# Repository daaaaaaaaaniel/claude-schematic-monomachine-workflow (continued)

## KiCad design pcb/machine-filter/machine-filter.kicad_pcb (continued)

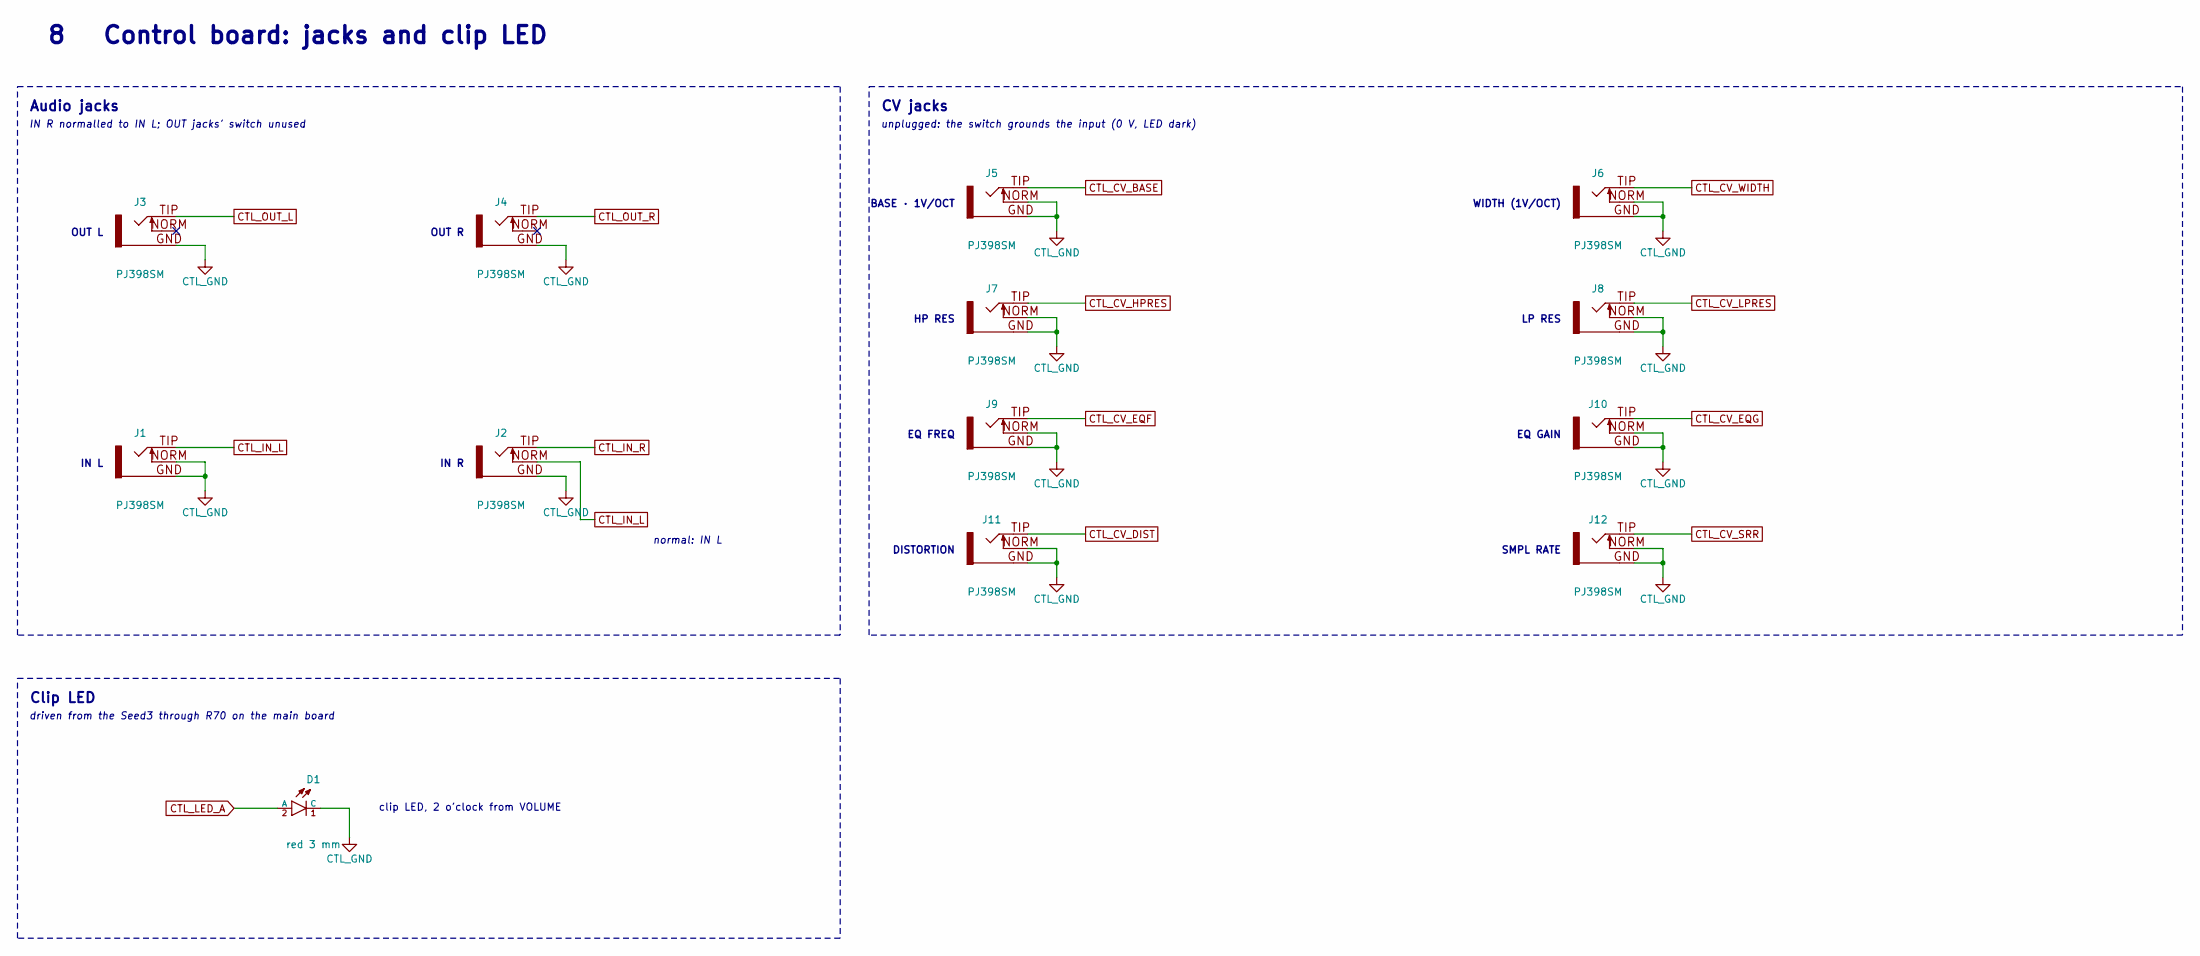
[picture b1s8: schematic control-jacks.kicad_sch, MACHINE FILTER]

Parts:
D1: red 3 mm; LED_3mm_C1A2; MPN 3 mm red LED, diffused
J1, J2, J3, J4: PJ398SM; PJ398SM_Jack_ES; MPN Thonkiconn PJ398SM
J5, J6, J7, J8, J9, J10, J11, J12: PJ398SM; PJ398SM_Jack_4ms_BentGND; MPN Thonkiconn PJ398SM, sleeve leg bent to 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

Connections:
CTL_CV_BASE: J5.TIP; also elsewhere on the board
CTL_CV_DIST: J11.TIP; also elsewhere on the board
CTL_CV_EQF: J9.TIP; also elsewhere on the board
CTL_CV_EQG: J10.TIP; also elsewhere on the board
CTL_CV_HPRES: J7.TIP; also elsewhere on the board
CTL_CV_LPRES: J8.TIP; also elsewhere on the board
CTL_CV_SRR: J12.TIP; also elsewhere on the board
CTL_CV_WIDTH: J6.TIP; also elsewhere on the board
CTL_GND: D1.1 (C), J1.GND, J1.NORM, J2.GND, J3.GND, J4.GND, J5.GND, J5.NORM, J6.GND, J6.NORM, J7.GND, J7.NORM, J8.GND, J8.NORM, J9.GND, J9.NORM, J10.GND, J10.NORM, J11.GND, J11.NORM, J12.GND, J12.NORM; also elsewhere on the board
CTL_IN_L: J1.TIP, J2.NORM; also elsewhere on the board
CTL_IN_R: J2.TIP; also elsewhere on the board
CTL_LED_A: D1.2 (A); also elsewhere on the board
CTL_OUT_L: J3.TIP; also elsewhere on the board
CTL_OUT_R: J4.TIP; also elsewhere on the board

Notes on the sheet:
Audio jacks
IN R normalled to IN L; OUT jacks' switch unused
OUT L
OUT R
IN L
IN R
normal: IN L
CV jacks
unplugged: the switch grounds the input (0 V, LED dark)
BASE · 1V/OCT
WIDTH (1V/OCT)
HP RES
LP RES
EQ FREQ
EQ GAIN
DISTORTION
SMPL RATE
Clip LED
driven from the Seed3 through R70 on the main board
clip LED, 2 o'clock from VOLUME
8 Control board: jacks and clip LED

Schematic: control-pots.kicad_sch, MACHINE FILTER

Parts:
C80: 100n; C_Disc_D3.0mm_W1.6mm_P2.50mm; MPN 100 nF 50 V X7R ceramic, 2.5 mm pitch
RV1, RV2, RV3, RV4, RV5, RV6, RV7, RV8, RV9: B10k; Pot_9mm_SnapIn_ES; MPN Alpha RD901F 9 mm B10k (any shaft)
U6: 74HC4051; SOIC-16_3.9x9.9mm_Pitch1.27mm; MPN 74HC4051D,653; LCSC C9386

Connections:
CTL_+3V3_A: C80.1, RV1.3, RV2.3, RV3.3, RV4.3, RV5.3, RV6.3, RV7.3, RV8.3, RV9.3, U6.16 (VCC); also elsewhere on the board
CTL_GND: C80.2, RV1.1, RV2.1, RV3.1, RV4.1, RV5.1, RV6.1, RV7.1, RV8.1, RV9.1, U6.6 (~E), U6.7 (VEE), U6.8 (GND); also elsewhere on the board
CTL_MUX_A: U6.11 (S0); also elsewhere on the board
CTL_MUX_B: U6.10 (S1); also elsewhere on the board
CTL_MUX_C: U6.9 (S2); also elsewhere on the board
CTL_POT_MUX: U6.3 (A); also elsewhere on the board
CTL_POT_VOL: RV1.2; also elsewhere on the board
unnamed: RV6.2, U6.13 (A0)
unnamed: RV4.2, U6.14 (A1)
unnamed: RV2.2, U6.15 (A2)
unnamed: RV8.2, U6.12 (A3)
unnamed: RV3.2, U6.1 (A4)
unnamed: RV9.2, U6.5 (A5)
unnamed: RV5.2, U6.2 (A6)
unnamed: RV7.2, U6.4 (A7)

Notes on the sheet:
Pots and pot multiplexer
pots: CCW end to GND, CW end to +3V3_A (from the main board); VOLUME has its own ADC pin, the other eight share one
EQ FREQ
HP RES
BASE · 1V/OCT
DISTORTION
WIDTH (1V/OCT)
SMPL RATE
LP RES
EQ GAIN
VOLUME
U6 passes one of the 8 pot wipers to POT_MUX; the Seed selects it with MUX_A/B/C (S0/S1/S2).
CTL_POT_MUX, CTL_POT_VOL, CTL_MUX_A/B/C go to the Seed3 on the main board, through the board connector (page 12).
Channel order follows the floorplan (design/pinmap.py); the firmware maps it.
9 Control board: pots and pot multiplexer

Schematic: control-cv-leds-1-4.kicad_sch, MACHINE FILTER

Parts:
C81, C82: 100n; C_Disc_D3.0mm_W1.6mm_P2.50mm; MPN 100 nF 50 V X7R ceramic, 2.5 mm pitch
D2, D3, D4, D5: red/green 3 mm; LED_3mm_Raised; MPN 3 mm red/green bicolour LED, 2 leads (a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
R71, R72, R73, R74: 1.5k; R_Axial_DIN0204_L3.6mm_D1.6mm_P5.08mm_Horizontal; MPN 1.5k 1/8 W 1% metal film, axial DIN0204
R80, R81, R82, R83: 10k; R_Axial_DIN0204_L3.6mm_D1.6mm_P5.08mm_Horizontal; MPN 10k 1/8 W 1% metal film, axial DIN0204
R90, R91, R92, R93: 1M; R_Axial_DIN0204_L3.6mm_D1.6mm_P5.08mm_Horizontal; MPN 1M 1/8 W 1% metal film, axial DIN0204
U7: LM324; SOIC-14_3.9x8.65mm_Pitch1.27mm; MPN LM324DT; LCSC C71035

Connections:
CTL_+12V: C81.1, U7.4 (V+); also elsewhere on the board
CTL_-12V: C82.2, U7.11 (V-); also elsewhere on the board
CTL_CV_BASE: R80.1; also elsewhere on the board
CTL_CV_HPRES: R82.1; also elsewhere on the board
CTL_CV_LPRES: R83.1; also elsewhere on the board
CTL_CV_WIDTH: R81.1; also elsewhere on the board
CTL_GND: C81.2, C82.1, R71.2, R72.2, R73.2, R74.2, R90.2, R91.2, R92.2, R93.2; also elsewhere on the board
unnamed: D2.2 (AK), R71.1, U7.13 (-)
unnamed: D2.1 (KA), U7.14
unnamed: D3.2 (AK), R72.1, U7.2 (-)
unnamed: D3.1 (KA), U7.1
unnamed: D4.2 (AK), R73.1, U7.9 (-)
unnamed: D4.1 (KA), U7.8
unnamed: D5.2 (AK), R74.1, U7.6 (-)
unnamed: D5.1 (KA), U7.7
unnamed: R81.2, R91.1, U7.3 (+)
unnamed: R83.2, R93.1, U7.5 (+)
unnamed: R82.2, R92.1, U7.10 (+)
unnamed: R80.2, R90.1, U7.12 (+)

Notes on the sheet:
CV 1: BASE · 1V/OCT LED
LED current = CV / 1.5k
green +, red -
CV 2: WIDTH (1V/OCT) LED
CV 3: HP RES LED
CV 4: LP RES LED
Op-amp supplies
U7: LM324, LED drivers
Each CV jack also lights a 2-lead red/green LED by it:
an LM324 with the LED in its feedback loop (after Mutable Instruments' Shades):
LED current = CV / 1.5k, no dead zone, levelling off near 5.5-6 mA from about ±8.5 V.
10k: input protection; 1M: an undriven cable reads 0 V, LED dark.
Through-hole resistors and capacitors (hand-soldered); U7, U8 SOIC (hand-soldered).
10 Control board: CV LEDs 1-4, LED drivers

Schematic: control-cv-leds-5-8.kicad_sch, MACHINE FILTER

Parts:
C83, C84: 100n; C_Disc_D3.0mm_W1.6mm_P2.50mm; MPN 100 nF 50 V X7R ceramic, 2.5 mm pitch
D6, D7, D8, D9: red/green 3 mm; LED_3mm_Raised; MPN 3 mm red/green bicolour LED, 2 leads (a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
R75, R76, R77, R78: 1.5k; R_Axial_DIN0204_L3.6mm_D1.6mm_P5.08mm_Horizontal; MPN 1.5k 1/8 W 1% metal film, axial DIN0204
R84, R85, R86, R87: 10k; R_Axial_DIN0204_L3.6mm_D1.6mm_P5.08mm_Horizontal; MPN 10k 1/8 W 1% metal film, axial DIN0204
R94, R95, R96, R97: 1M; R_Axial_DIN0204_L3.6mm_D1.6mm_P5.08mm_Horizontal; MPN 1M 1/8 W 1% metal film, axial DIN0204
U8: LM324; SOIC-14_3.9x8.65mm_Pitch1.27mm; MPN LM324DT; LCSC C71035

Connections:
CTL_+12V: C83.1, U8.4 (V+); also elsewhere on the board
CTL_-12V: C84.2, U8.11 (V-); also elsewhere on the board
CTL_CV_DIST: R86.1; also elsewhere on the board
CTL_CV_EQF: R84.1; also elsewhere on the board
CTL_CV_EQG: R85.1; also elsewhere on the board
CTL_CV_SRR: R87.1; also elsewhere on the board
CTL_GND: C83.2, C84.1, R75.2, R76.2, R77.2, R78.2, R94.2, R95.2, R96.2, R97.2; also elsewhere on the board
unnamed: D6.2 (AK), R75.1, U8.13 (-)
unnamed: D6.1 (KA), U8.14
unnamed: D7.2 (AK), R76.1, U8.2 (-)
unnamed: D7.1 (KA), U8.1
unnamed: D8.2 (AK), R77.1, U8.9 (-)
unnamed: D8.1 (KA), U8.8
unnamed: D9.2 (AK), R78.1, U8.6 (-)
unnamed: D9.1 (KA), U8.7
unnamed: R85.2, R95.1, U8.3 (+)
unnamed: R87.2, R97.1, U8.5 (+)
unnamed: R86.2, R96.1, U8.10 (+)
unnamed: R84.2, R94.1, U8.12 (+)

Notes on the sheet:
CV 5: EQ FREQ LED
LED current = CV / 1.5k
green +, red -
CV 6: EQ GAIN LED
CV 7: DISTORTION LED
CV 8: SMPL RATE LED
Op-amp supplies
U8: LM324, LED drivers
Each CV jack also lights a 2-lead red/green LED by it:
an LM324 with the LED in its feedback loop (after Mutable Instruments' Shades):
LED current = CV / 1.5k, no dead zone, levelling off near 5.5-6 mA from about ±8.5 V.
10k: input protection; 1M: an undriven cable reads 0 V, LED dark.
Through-hole resistors and capacitors (hand-soldered); U7, U8 SOIC (hand-soldered).
11 Control board: CV LEDs 5-8, LED drivers

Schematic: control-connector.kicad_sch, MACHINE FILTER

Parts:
JA1, JA3: 1x7 socket; PinSocket_1x07_P2.54mm_Vertical; MPN 2.54 mm female header 1x7, 8.5 mm (as t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
JA2: 1x11 socket; PinSocket_1x11_P2.54mm_Vertical; MPN 2.54 mm female header 1x11, 8.5 mm (as 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
JA4: 1x9 socket; PinSocket_1x09_P2.54mm_Vertical; MPN 2.54 mm female header 1x9, 8.5 mm (as t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

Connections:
CTL_+3V3_A: JA2.4; also elsewhere on the board
CTL_+12V: JA3.2; also elsewhere on the board
CTL_-12V: JA4.2; also elsewhere on the board
CTL_CV_BASE: JA2.9; also elsewhere on the board
CTL_CV_DIST: JA4.7; also elsewhere on the board
CTL_CV_EQF: JA4.8; also elsewhere on the board
CTL_CV_EQG: JA4.5; also elsewhere on the board
CTL_CV_HPRES: JA2.6; also elsewhere on the board
CTL_CV_LPRES: JA2.7; also elsewhere on the board
CTL_CV_SRR: JA4.4; also elsewhere on the board
CTL_CV_WIDTH: JA2.10; also elsewhere on the board
CTL_GND: JA1.1, JA1.4, JA1.6, JA2.3, JA2.5, JA2.8, JA2.11, JA3.1, JA3.3, JA4.1, JA4.3, JA4.6, JA4.9; also elsewhere on the board
CTL_IN_L: JA1.5; also elsewhere on the board
CTL_IN_R: JA1.7; also elsewhere on the board
CTL_LED_A: JA3.4; also elsewhere on the board
CTL_MUX_A: JA3.5; also elsewhere on the board
CTL_MUX_B: JA3.7; also elsewhere on the board
CTL_MUX_C: JA3.6; also elsewhere on the board
CTL_OUT_L: JA1.3; also elsewhere on the board
CTL_OUT_R: JA1.2; also elsewhere on the board
CTL_POT_MUX: JA2.1; also elsewhere on the board
CTL_POT_VOL: JA2.2; also elsewhere on the board

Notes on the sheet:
Board-to-board connector
4 single-row 2.54 mm headers: JA* female on the control board's back, JB* male on the main board's front
JA1: pin 1 at (36.83, 16.51) mm,
panel frame; pins run down (main side)
JA2: pin 1 at (43.18, 52.07) mm,
panel frame; pins run up (main side)
JA3: pin 1 at (5.08, 55.88) mm,
panel frame; pins run right (main side)
JA4: pin 1 at (43.18, 110.49) mm,
Supplies from the main board (PWR_FLAG: driven through the connector)
Header groups, positions and pin order come from the floorplan (design/headers.py): analog pairs, then digital pairs, a GND after each pair; supplies between GNDs.
12 Control board: board-to-board connector

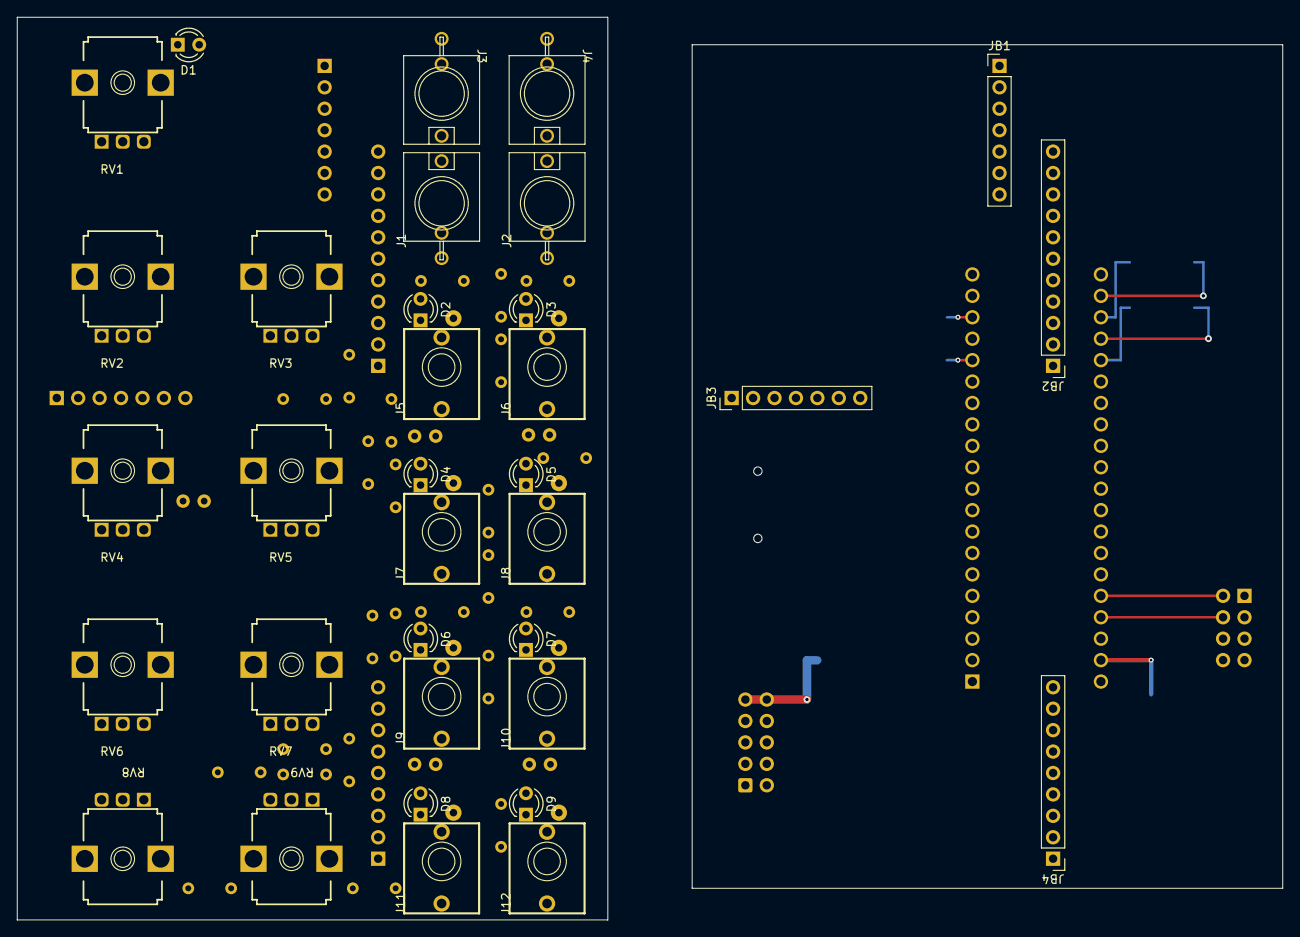
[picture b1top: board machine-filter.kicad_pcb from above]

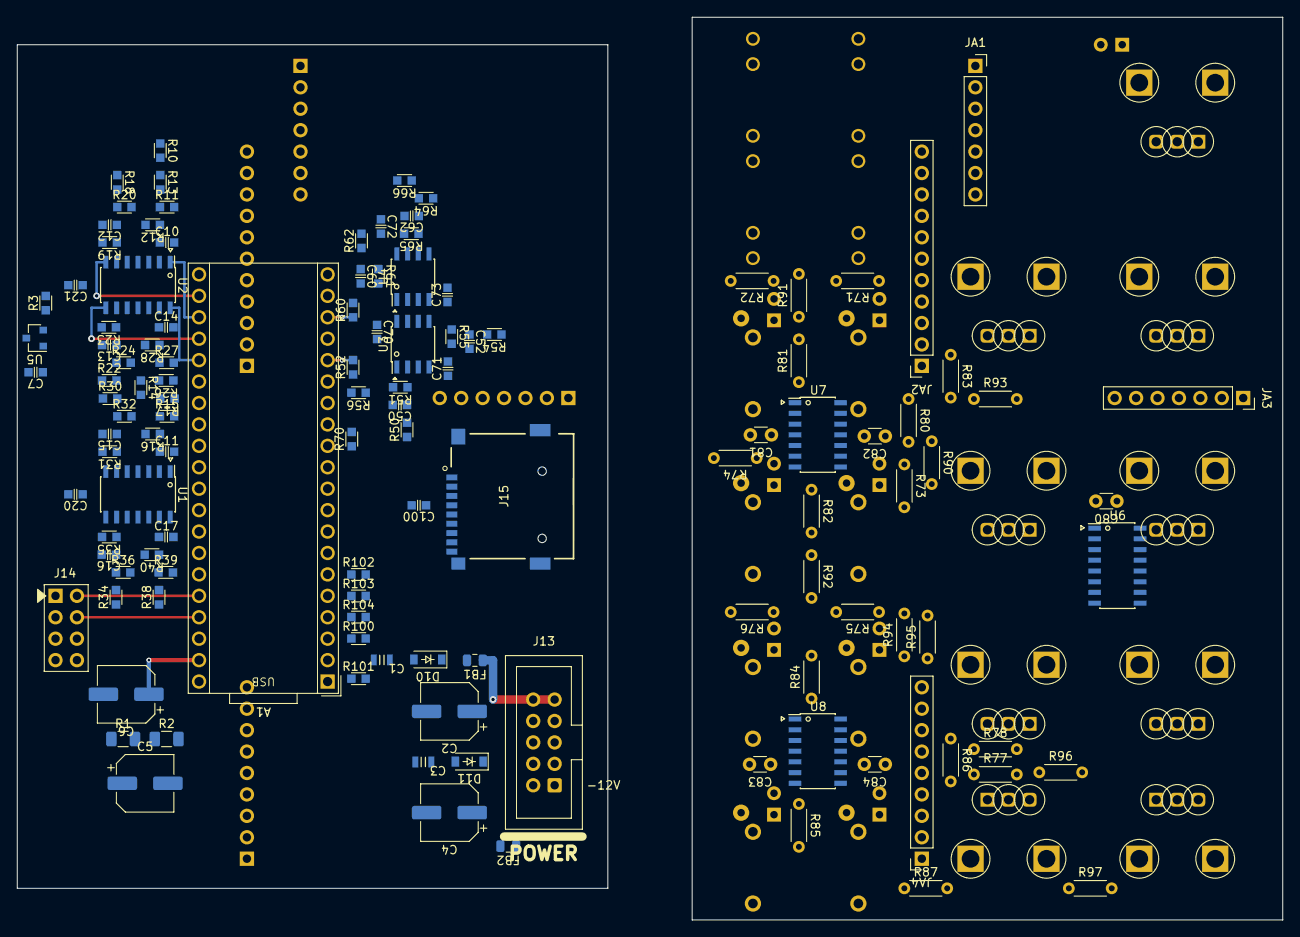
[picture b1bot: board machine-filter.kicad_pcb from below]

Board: 2 copper layers, 150.0 x 107.0 mm, 156 parts (122 on the bottom side), 125 nets.

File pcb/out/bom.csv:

"Reference","Value","Footprint","LCSC","MPN","Board","Assembly","DNP","QUANTITY"
"A1","Daisy Seed3","filter-module:Daisy_Seed_ES_Sockets","","Electrosmith Daisy Seed3 on 2x 1x20 2.54 mm sockets","main","hand","","1"
"C1,C3","10u 25V","filter-module:C_0805","C15850","CL21A106KAYNNNE","main","JLC (SMD)","","2"
"C2,C4-C6","100u 35V","Capacitor_SMD:CP_Elec_6.3x7.7","C72478","RVT1V101M0607","main","JLC (SMD)","","4"
"C7,C20,C21,C70-C73,C100","100n","filter-module:C_0603","C14663","CC0603KRX7R9BB104","main","JLC (SMD)","","8"
"C10-C17","1n","filter-module:C_0603","C1588","CL10B102KB8NNNC","main","JLC (SMD)","","8"
"C50,C52","330p","filter-module:C_0603","C1664","CL10C331JB8NNNC","main","JLC (SMD)","","2"
"C60,C62","47p","filter-module:C_0603","C1671","CL10C470JB8NNNC","main","JLC (SMD)","","2"
"C80-C84","100n","Capacitor_THT:C_Disc_D3.0mm_W1.6mm_P2.50mm","","100 nF 50 V X7R ceramic, 2.5 mm pitch","control","hand","","5"
"D1","red 3 mm","filter-module:LED_3mm_C1A2","","3 mm red LED, diffused","control","hand","","1"
"D2-D9","red/green 3 mm","filter-module:LED_3mm_Raised","","3 mm red/green bicolour LED, 2 leads (anti-parallel), diffused","control","hand","","8"
"D10,D11","B5819W","filter-module:D_SOD-123","C8598","B5819W SL","main","JLC (SMD)","","2"
"FB1,FB2","600R@100MHz 0.5A","filter-module:R_0805_2012Metric","C1017","GZ2012D601TF","main","JLC (SMD)","","2"
"J1-J4","PJ398SM","filter-module:PJ398SM_Jack_ES","","Thonkiconn PJ398SM","control","hand","","4"
"J5-J12","PJ398SM","filter-module:PJ398SM_Jack_4ms_BentGND","","Thonkiconn PJ398SM, sleeve leg bent to the footprint","control","hand","","8"
"J13","EURO PWR 2x5","filter-module:Pins_2x05_2.54mm_TH_EurorackPower_Shrouded","","2x5 2.54 mm shrouded box header","main","hand","","1"
"J14","EXPANSION 2x4","filter-module:Pins_2x04_2.54mm_TH","","2x4 2.54 mm pin header, unshrouded (d)","main","hand","","1"
"J15","TF-01A","filter-module:TF-01A","C91145","HRO TF-01A microSD socket, push-push (optional, DNP)","main","JLC (SMD)","DNP","1"
"JA1,JA3","1x7 socket","Connector_PinSocket_2.54mm:PinSocket_1x07_P2.54mm_Vertical","","2.54 mm female header 1x7, 8.5 mm (as the Seed3 sockets)","control","hand","","2"
"JA2","1x11 socket","Connector_PinSocket_2.54mm:PinSocket_1x11_P2.54mm_Vertical","","2.54 mm female header 1x11, 8.5 mm (as the Seed3 sockets)","control","hand","","1"
"JA4","1x9 socket","Connector_PinSocket_2.54mm:PinSocket_1x09_P2.54mm_Vertical","","2.54 mm female header 1x9, 8.5 mm (as the Seed3 sockets)","control","hand","","1"
"JB1,JB3","1x7 header","Connector_PinHeader_2.54mm:PinHeader_1x07_P2.54mm_Vertical","","2.54 mm male pin header 1x7","main","hand","","2"
"JB2","1x11 header","Connector_PinHeader_2.54mm:PinHeader_1x11_P2.54mm_Vertical","","2.54 mm male pin header 1x11","main","hand","","1"
"JB4","1x9 header","Connector_PinHeader_2.54mm:PinHeader_1x09_P2.54mm_Vertical","","2.54 mm male pin header 1x9","main","hand","","1"
"R1,R2","3.3 0.75W","filter-module:R_1206_3216Metric","C2577888","SG73P2BTTD3R30F","main","JLC (SMD)","","2"
"R3,R70","1k","filter-module:R_0603","C21190","0603WAF1001T5E","main","JLC (SMD)","","2"
"R10,R14","100k 0.1%","filter-module:R_0603","C122538","RT0603BRD07100KL","main","JLC (SMD)","","2"
"R11,R13,R15,R17","20k 0.1%","filter-module:R_0603","C723637","RT0603BRD0720KL","main","JLC (SMD)","","4"
"R12,R16","120k 25ppm","filter-module:R_0603","C862537","RT0603DRD07120KL","main","JLC (SMD)","","2"
"R18,R20,R22,R24,R26,R28,R30,R32,R34,R36,R38,R40","120k","filter-module:R_0603","C25808","0603WAF1203T5E","main","JLC (SMD)","","12"
"R19,R23,R27,R31,R35,R39","20k","filter-module:R_0603","C4184","0603WAF2002T5E","main","JLC (SMD)","","6"
"R50,R54","100k","filter-module:R_0603","C25803","0603WAF1003T5E","main","JLC (SMD)","","2"
"R51,R55,R60,R64","10k","filter-module:R_0603","C25804","0603WAF1002T5E","main","JLC (SMD)","","4"
"R52,R56,R62,R66","100","filter-module:R_0603","C22775","0603WAF1000T5E","main","JLC (SMD)","","4"
"R61,R65","51k","filter-module:R_0603","C23196","0603WAF5102T5E","main","JLC (SMD)","","2"
"R71-R78","1.5k","Resistor_THT:R_Axial_DIN0204_L3.6mm_D1.6mm_P5.08mm_Horizontal","","1.5k 1/8 W 1% metal film, axial DIN0204","control","hand","","8"
"R80-R87","10k","Resistor_THT:R_Axial_DIN0204_L3.6mm_D1.6mm_P5.08mm_Horizontal","","10k 1/8 W 1% metal film, axial DIN0204","control","hand","","8"
"R90-R97","1M","Resistor_THT:R_Axial_DIN0204_L3.6mm_D1.6mm_P5.08mm_Horizontal","","1M 1/8 W 1% metal film, axial DIN0204","control","hand","","8"
"R100-R104","47k","filter-module:R_0603","C25819","0603WAF4702T5E","main","JLC (SMD)","","5"
"RV1-RV9","B10k","filter-module:Pot_9mm_SnapIn_ES","","Alpha RD901F 9 mm B10k (any shaft)","control","hand","","9"
"U1,U2","LMV324","filter-module:SOIC-14_3.9x8.65mm_Pitch1.27mm","C7974","LMV324IDR","main","JLC (SMD)","","2"
"U3,U4","TL072","filter-module:SOIC-8_3.9x4.9mm_Pitch1.27mm","C6961","TL072CDT","main","JLC (SMD)","","2"
"U5","LM4040-10","filter-module:SOT-23","C201738","LM4040C10IDBZR","main","JLC (SMD)","","1"
"U6","74HC4051","filter-module:SOIC-16_3.9x9.9mm_Pitch1.27mm","C9386","74HC4051D,653","control","hand","","1"
"U7,U8","LM324","filter-module:SOIC-14_3.9x8.65mm_Pitch1.27mm","C71035","LM324DT","control","hand","","2"

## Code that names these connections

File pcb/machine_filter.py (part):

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
# Seed3 pins (Electrosmith Seed3_pinout.csv). ADC pins from design/pinmap.py; MIDI on pins 14/15 (D13/D14, USART1).
# Which pins may trade places: design/swap_groups.py.
SEED_PINS = {"2": "SD_D3", "3": "SD_D2", "4": "SD_D1", "5": "SD_D0", "6": "SD_CMD", "7": "SD_CK", "8": "MUX_A", "9": "MUX_B", "10": "MUX_C", "12": "LED_CLIP",
             "16": "CODEC_IN_L", "17": "CODEC_IN_R", "18": "CODEC_OUT_L", "19": "CODEC_OUT_R",
             "36": "USB_DM", "37": "USB_DP"}
SEED_PINS.update({pin: sig for sig, pin in PM.SEED_ADC.items()})
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    j14 = stock("Connector_Generic", "Conn_02x04_Odd_Even", "J14", "EXPANSION 2x4", f"{FM}:Pins_2x04_2.54mm_TH",
                mpn="2x4 2.54 mm pin header, unshrouded")
    # D+ on pin 4, ground on pin 3 (d, 2026-10-07): both USB lines reach the near pin column in a straight line
    for pin, net in {"2": "USB_DM", "4": "USB_DP", "5": "MIDI_TX", "6": "MIDI_RX"}.items():
        j14[pin] += N(net)
    j14[1, 3, 8] += GND
    j14[7] += D33
    # optional microSD socket (as the Dev Kit): SDMMC1 on pins 2-7, 47k pull-ups on CMD and D0-D3; the socket is DNP
    j15 = stock(FM, "MicroSD_TF-01A", "J15", "TF-01A", f"{FM}:TF-01A", "C91145",
                "HRO TF-01A microSD socket, push-push (optional, DNP)")
    for pin, net in {"1": "SD_D2", "2": "SD_D3", "3": "SD_CMD", "5": "SD_CK", "7": "SD_D0", "8": "SD_D1"}.items():
        j15[pin] += N(net)
    j15["4"] += D33
    j15["6", "MP1", "MP2", "MP3", "MP4"] += GND
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
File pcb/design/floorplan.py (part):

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    adc_unit, _ = match(CV, slots, lambda n, qs: dist(hpin[f"CV_{n}"], P(quads[qs[0]], SECTION[qs[1]][1])))
    # signals -> ADC pins (weighted: the scaled side is sensitive; the 1V/OCT inputs most of all)
    src = {f"ADC_{n}": P(quads[adc_unit[n][0]], SECTION[adc_unit[n][1]][0]) for n in CV}
    src.update(POT_MUX=hpin["POT_MUX"], POT_VOL=hpin["POT_VOL"])
    w = {s: (W_1VOCT if s[4:] in boards.ONE_V_OCT else W_SENSITIVE) if s.startswith("ADC_") else W_SLOW for s in src}
    adc_pin, adc_cost = match(list(src), ADC_PINS, lambda s, p: w[s] * dist(src[s], sp[p]))
    codec_cost = W_SENSITIVE * (dist(P(u3, "1"), sp["16"]) + dist(P(u3, "7"), sp["17"]) +
                                dist(P(u4, "2"), sp["18"]) + dist(P(u4, "6"), sp["19"]))
    robust = W_ROBUST * (sum(dist(hpin[f"CV_{n}"], P(quads[q], SECTION[s][1])) for n, (q, s) in adc_unit.items()) +
                         dist(hpin["IN_L"], P(u3, "2")) + dist(hpin["IN_R"], P(u3, "6")) +
                         dist(P(u4, "1"), hpin["OUT_L"]) + dist(P(u4, "7"), hpin["OUT_R"]))
    slow = W_SLOW * (dist(hpin["MUX_A"], sp["8"]) + dist(hpin["MUX_B"], sp["9"]) + dist(hpin["MUX_C"], sp["10"]) +
                     dist(hpin["LED_A"], sp["12"]))
    res = dict(board=B, seed=seed_pos, sp=sp, adc_unit=adc_unit, adc_pin=adc_pin, src=src, hpin=hpin,
               cost=adc_cost + codec_cost + robust + slow,
               parts=dict(adc=adc_cost, codec=codec_cost, robust=robust, slow=slow))
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         "MUX_PIN = {" + ", ".join(f'"{n}": "{p}"' for n, p in ctl["mux_pin"].items()) + "}",
         "MUX_SELECT = [" + ", ".join(f'"{n}"' for n, _ in sorted(ctl["mux_pin"].items(), key=lambda kv: chan[kv[1]]))
         + "]   # firmware: select 0..7 -> pot",
         'MIDI = {"MIDI_TX": "14", "MIDI_RX": "15"}   # D13 / D14 = USART1 TX / RX (PB6 / PB7), libDaisy\'s default',
         "CONTROL_PLACEMENT = " + repr({i["ref"]: (i["x"], i["y"], i["rot"]) for i in ctl["board"].items if "x" in i}),
         "MAIN_PLACEMENT = " + repr({i["ref"]: (i["x"], i["y"], i["rot"]) for i in mb["board"].items if "x" in i}), ""]
    open(os.path.join(HERE, "pinmap.py"), "w").write("\n".join(L))
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    sp = mb["sp"]
    pin_of = {v: k for k, v in mb["adc_pin"].items()}
    main_end = {"IN_L": P(q["U3"], "2"), "IN_R": P(q["U3"], "6"), "OUT_L": P(q["U4"], "1"), "OUT_R": P(q["U4"], "7"),
                "POT_VOL": sp[mb["adc_pin"]["POT_VOL"]], "POT_MUX": sp[mb["adc_pin"]["POT_MUX"]],
                "MUX_A": sp["8"], "MUX_B": sp["9"], "MUX_C": sp["10"], "LED_A": sp["12"], "+3V3_A": sp["21"],
                "+12V": P(q["J13"], "9"), "-12V": P(q["J13"], "1")}
    for n, (u, sec) in mb["adc_unit"].items():
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    P = lambda pp, pin: tuple(pp[pin][0][:2])
    rows = [dict(kind="adc_1voct" if s[4:] in boards.ONE_V_OCT else "adc", signal=s, seed_pin=p,
                 mm=round(dist(mb["src"][s], sp[p]), 1)) for s, p in mb["adc_pin"].items() if s.startswith("ADC_")]
    for name, a, pin in (("codec IN_L", P(u3, "1"), "16"), ("codec IN_R", P(u3, "7"), "17"),
                         ("codec OUT_L", P(u4, "2"), "18"), ("codec OUT_R", P(u4, "6"), "19")):
        rows.append(dict(kind="codec", signal=name, seed_pin=pin, mm=round(dist(a, sp[pin]), 1)))
    return rows
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
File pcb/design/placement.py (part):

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STEPS = [
    # 1. Seed3 (d: "place the Seed3"): USB end down, USB socket 26 mm inside the control board's edge (A2-C2
    #    agree). Its group: the supply filter R1-C5-R2-C6 ending at VIN (pin 39, bottom of the right row), and R70
    #    at pin 12 (LED_A). Critical trace: VIN pin 39 -> C6, the filter's last capacitor, at the pin.
    {"name": "seed3",
     "parts": {"A1": ("main", 33.615, 89.49, 0, "back"),   # KiCad rotation after its own (top-bottom) flip
               "C6": ("main", 57.5, 91.0, 0, "back"),
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     "traces": [("A1", "39", "C6", None, 0.5, "B.Cu")]},   # C6 pad: the one on VIN,
    # 2. U2, CV 1-4 group (d: "place the second primary part"). Back side, rotation 0: after KiCad's top-bottom
    #    flip, pins 1-7 run up the left side (facing the Seed3's ADC pins), 8-14 down the right. Pin 1 (BASE out)
    #    level with Seed3 pin 23 (ADC_BASE), so the critical trace is a straight 3 mm line. Each channel's parts sit
    #    by its section: A (BASE, pins 1-3) below, B (HP RES, 5-7) above, C (LP RES, 8-10) right-upper,
    #    D (EQ FREQ, 12-14) right-lower; C21 (decoupling) between them. The other three channels' ADC pins are
    #    re-matched once U1 is placed (pin map follows the layout).
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     # after the re-match (d: keep it), WIDTH is on U1 section A and Seed3 pin 29: a straight 3 mm trace
     "traces": [("U1", "1", "A1", "29", 0.25, "B.Cu")]},
    # 4. U3 (audio in) and U4 (audio out), d: "do both U3 and U4, and their critical traces". Left of the Seed3,
    #    by the codec pins (16/17 = CODEC_IN_L/R, 18/19 = CODEC_OUT_L/R). Back side, rotation 0 (pins 1-4 up the
    #    left, 8-5 up the right). U3 below U4. The four codec-side resistors stand in two columns between the
    #    op-amps and the Seed3's left row (2.54 mm pin pitch is less than a resistor's 3.25 mm courtyard), each with
    #    its codec pad level with its Seed3 pin, so every codec trace is a straight horizontal line that passes no
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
